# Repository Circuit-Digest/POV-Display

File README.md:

# [POV Display](https://circuitdigest.com/microcontroller-projects/diy-pov-display-using-ESP32-Arduino)

<br>

<br>

<be>

[DIY POV Display Tutorial using ESP32 Arduino](https://circuitdigest.com/microcontroller-projects/diy-pov-display-using-ESP32-Arduino)

[POV Display full Yoututbe Video](https://www.youtube.com/embed/gkemkTWuw_Q)

[<h1>Click here](https://circuitdigest.com/tags/ESP32) For other ESP32 tutorials.</h1>

<br>
<br>
<br>
<br>
<br>
<br>
<br>
Persistence of Vision is a fundamental principle that allows our eyes to perceive continuous motion from separate images, a concept crucial to the illusion of motion in cinema. When I was a kid, I was always fascinated with it. So, in this project, we are going to use this fascinating optical phenomenon to create a cool-looking POV Display. You must have seen a lot of such projects on the web, but most of them are limited to very low resolution and just display some texts and geometries. We plan to create a POV display that is not limited to just texts or simple shapes. Ours will be able to display images and animations with a resolution of 128 pixels. We have settled with this resolution because it's the sweet spot where we can get decent image quality and it would be easier to build.
 We settled on the ESP32 module as the brain of this display, because it is cheap, easy to get and powerful enough to run the display. The display will have two rotating arms, each outfitted with 64 LEDs, to create a total resolution of 128 pixels. The display will rotate at a constant speed, with the LEDs flashing in meticulously orchestrated patterns, controlled by the ESP32 microcontroller. This synchronization allows the display to generate images or text that appear to hover in mid-air, producing a smooth, continuous visual experience. 

<br>
[Note: As this projects are very simple we are only providing the code, schemaitic, and a few essential images if you want to get the images or code explanations do check out the Circuit Digest website.
<br>
<br>

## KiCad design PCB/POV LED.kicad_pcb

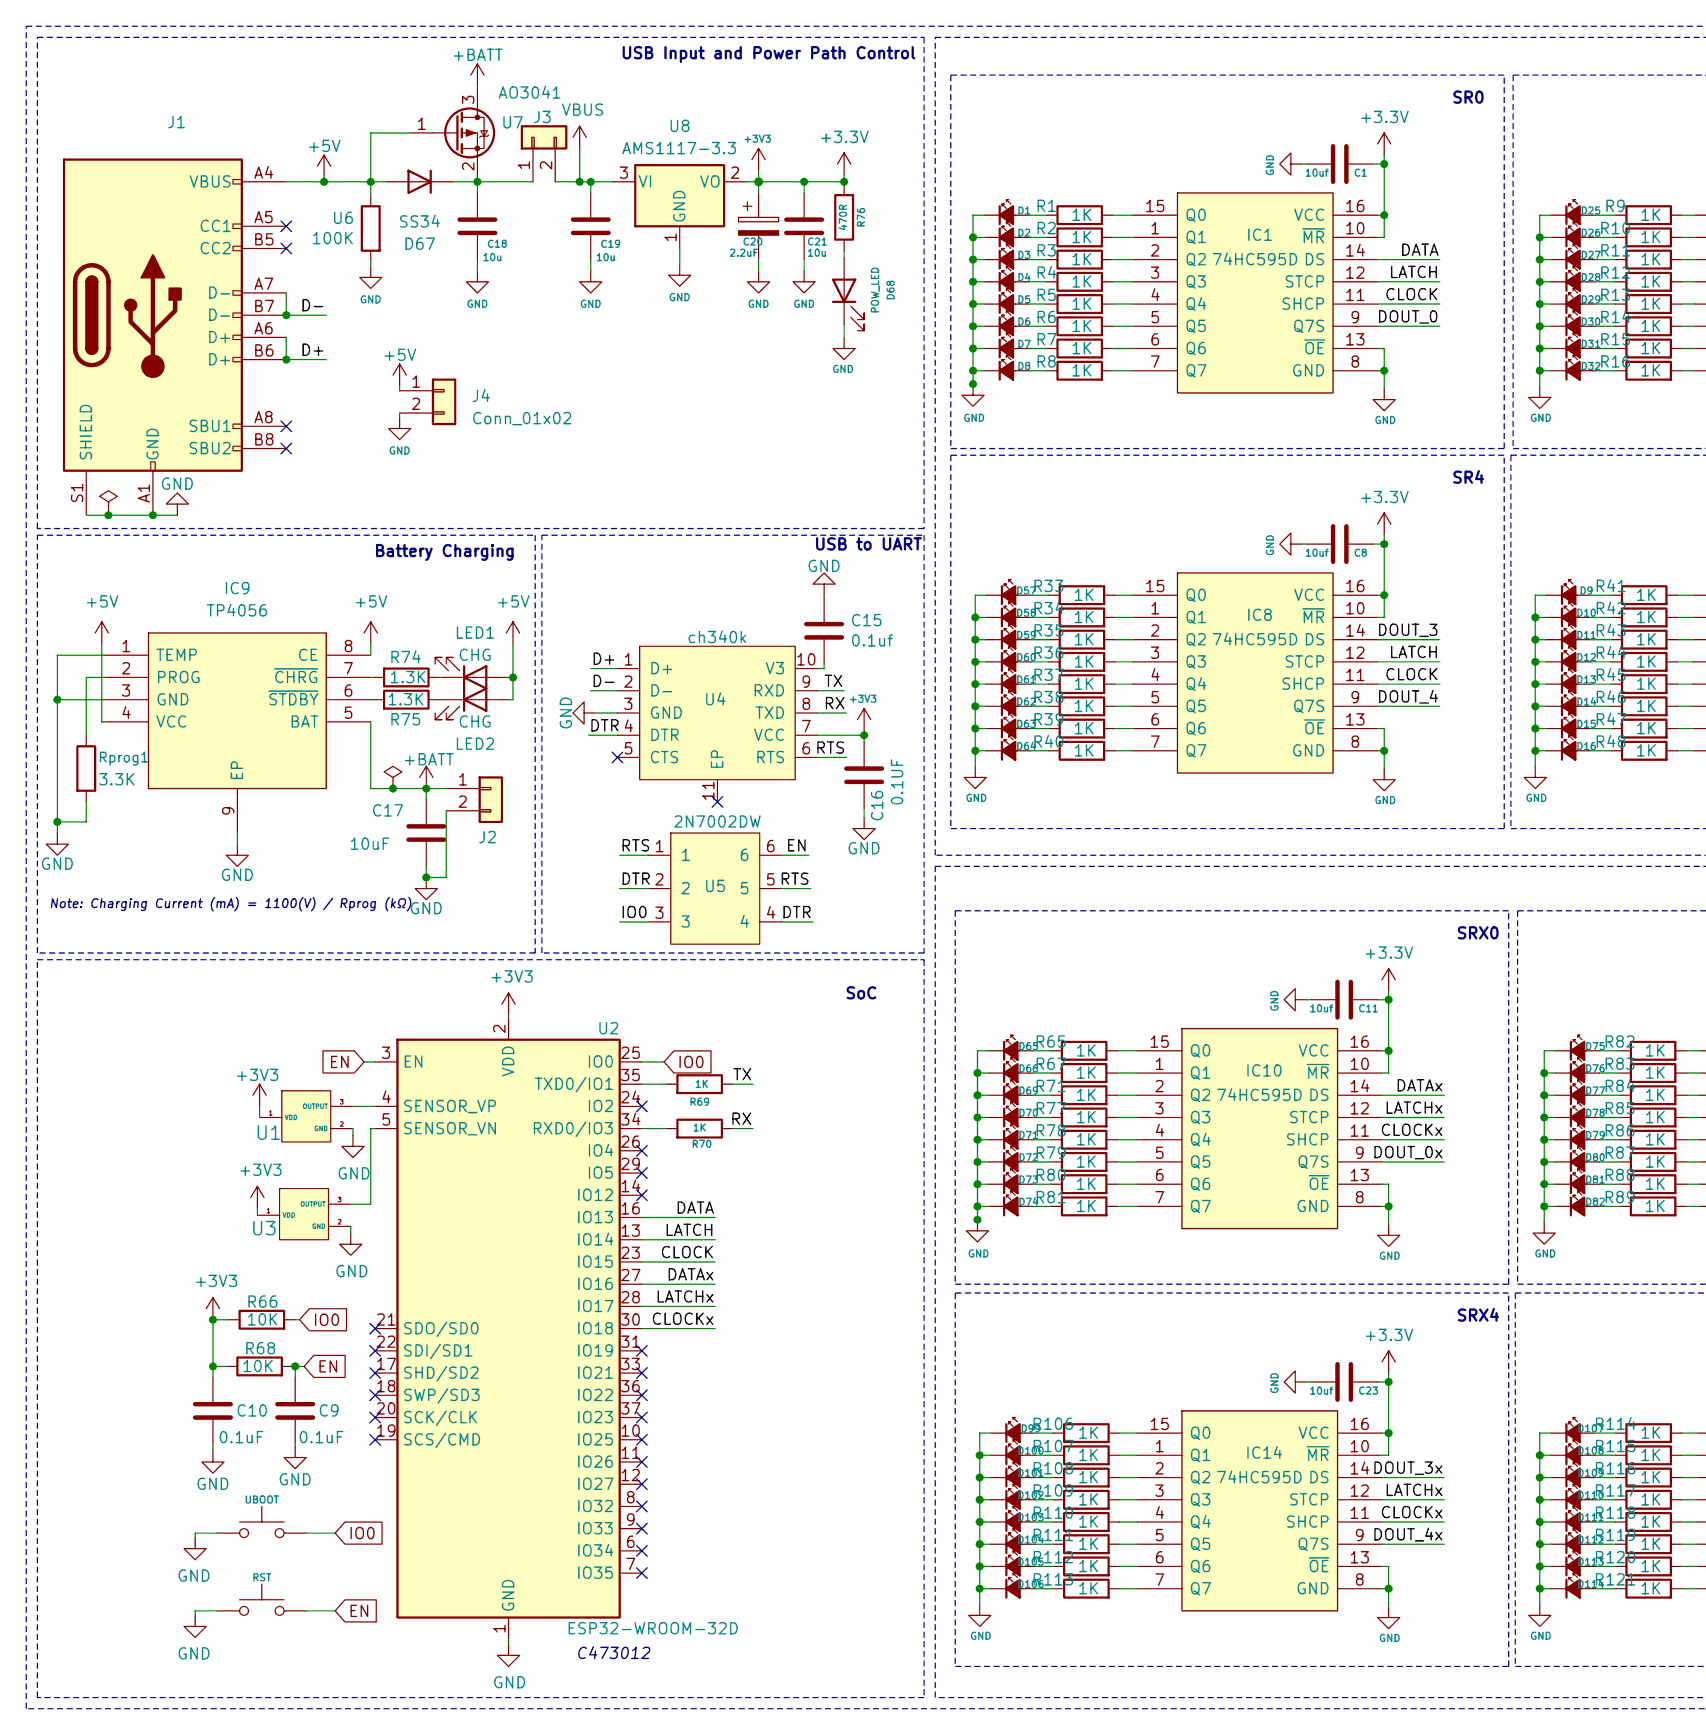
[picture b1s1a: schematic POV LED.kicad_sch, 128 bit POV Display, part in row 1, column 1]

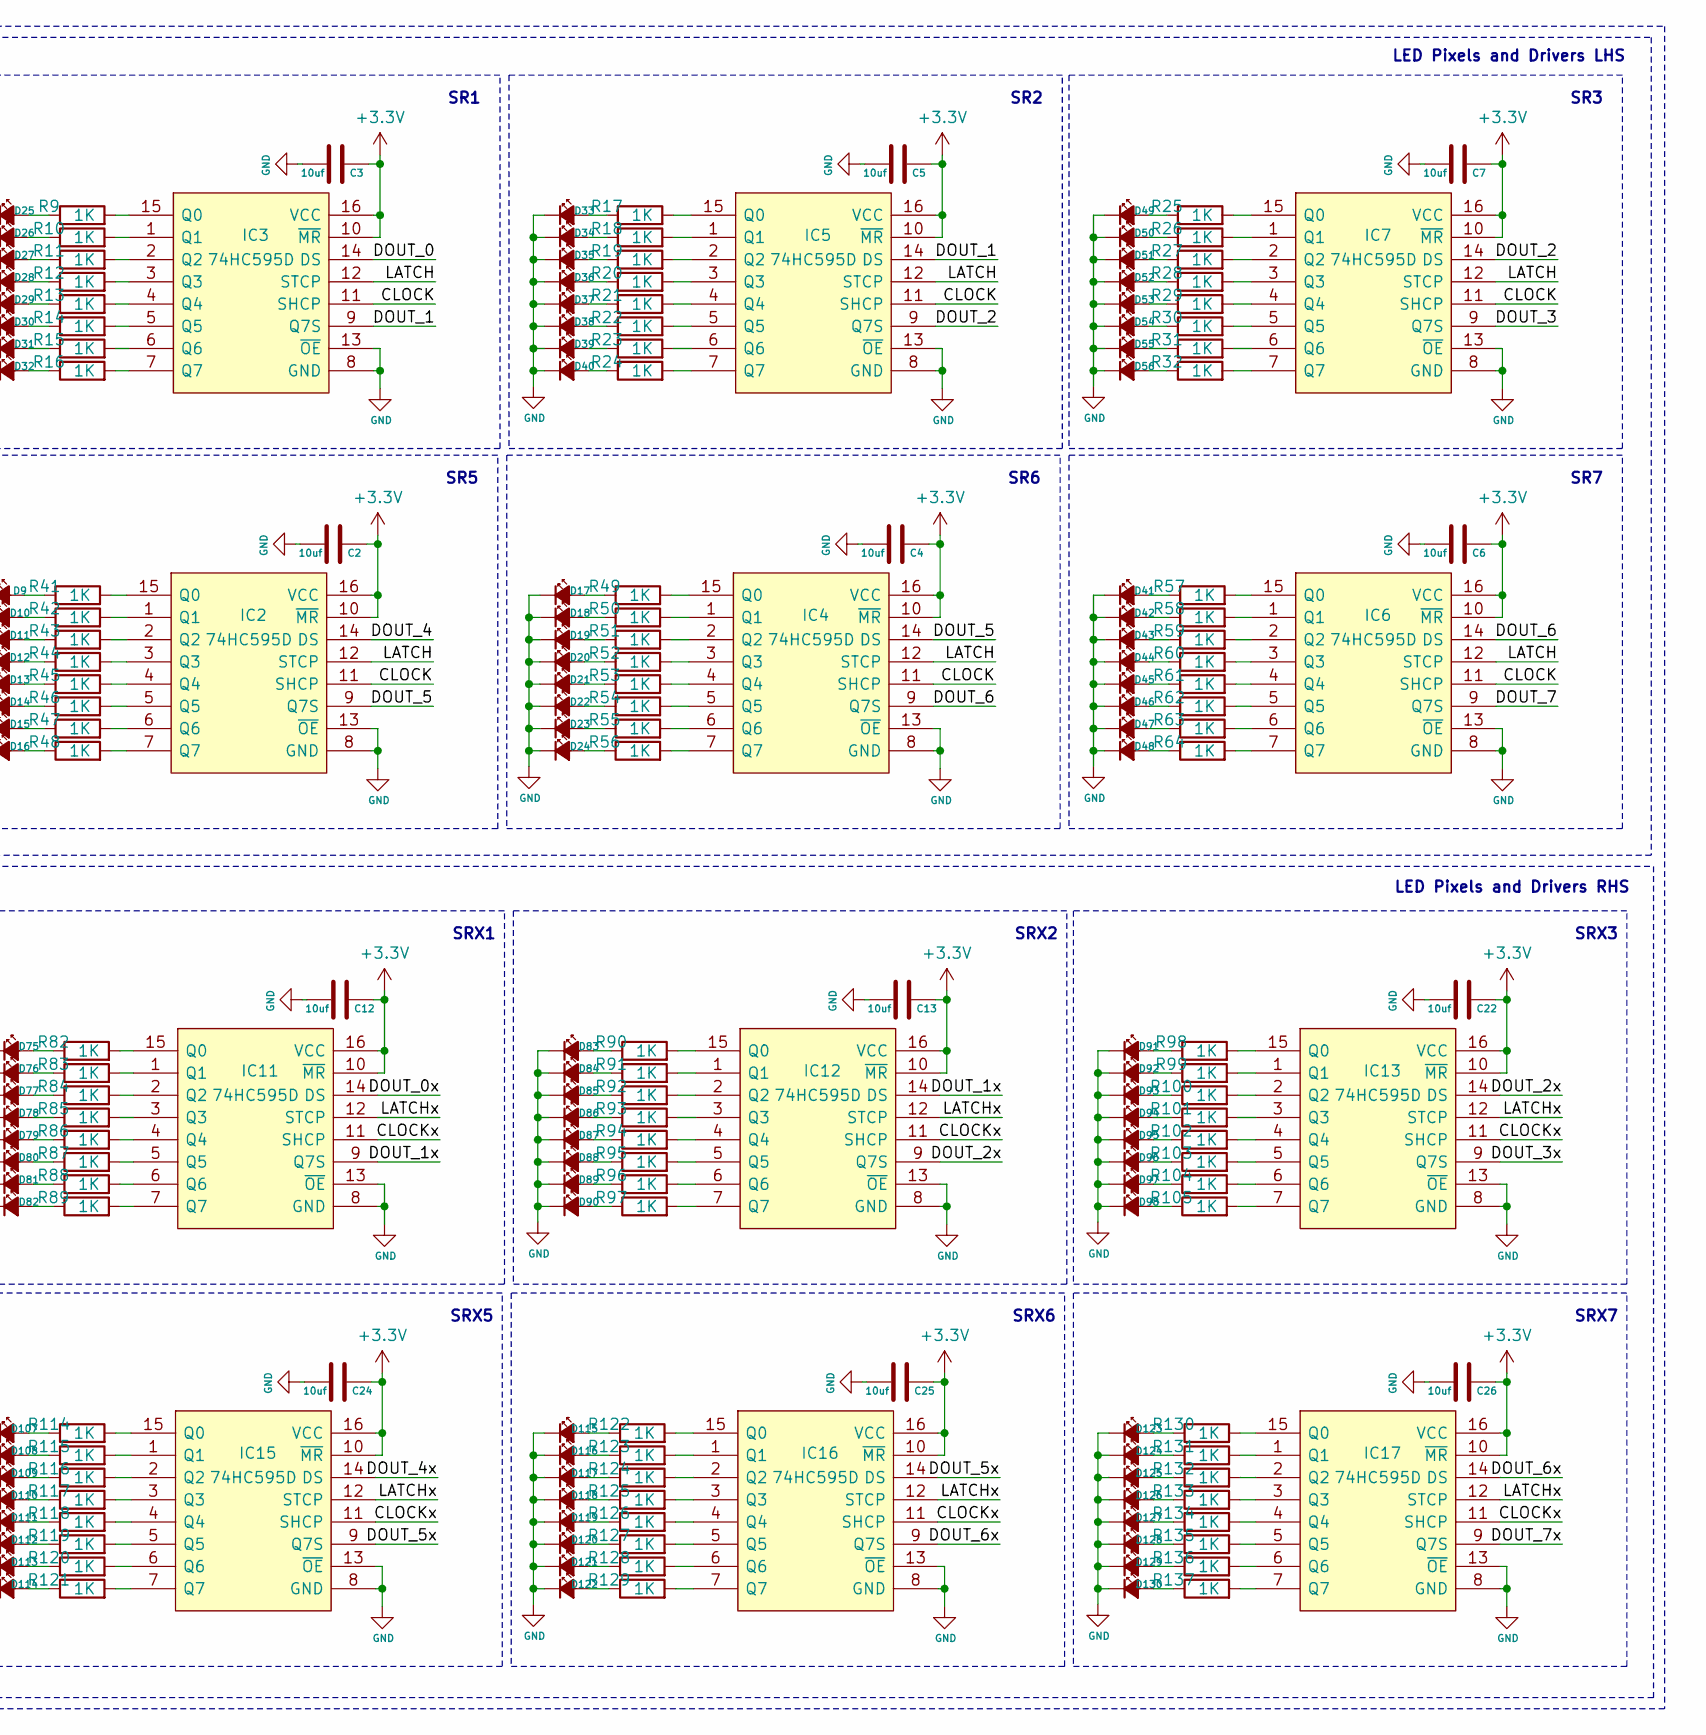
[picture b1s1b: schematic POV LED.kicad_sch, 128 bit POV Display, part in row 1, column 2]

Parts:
BOOT1: UBOOT; Tactile 3x4x2mm TS-A010
C1, C2, C3, C4, C5, C6, C7, C8, C11, C12, C13, C22, C23, C24, C25, C26: 10uf; C_0603_1608Metric
C9, C10: 0.1uF; C_0603_1608Metric
C15: 0.1uf; C_0603_1608Metric
C16: 0.1UF; C_0603_1608Metric
C17: 10uF; C_0603_1608Metric
C18, C19, C21: 10u; C_0603_1608Metric
C20: 2.2uF; C_0805_2012Metric
D1, D2, D3, D4, D5, D6, D7, D8, D9, D10, D11, D12, D13, D14, D15, D16, D17, D18, D19, D20, D21, D22, D23, D24, D25, D26, D27, D28, D29, D30, D31, D32, D33, D34, D35, D36, D37, D38, D39, D40, D41, D42, D43, D44, D45, D46, D47, D48, D49, D50, D51, D52, D53, D54, D55, D56, D57, D58, D59, D60, D61, D62, D63, D64, D65, D66, D69, D70, D71, D72, D73, D74, D75, D76, D77, D78, D79, D80, D81, D82, D83, D84, D85, D86, D87, D88, D89, D90, D91, D92, D93, D94, D95, D96, D97, D98, D99, D100, D101, D102, D103, D104, D105, D106, D107, D108, D109, D110, D111, D112, D113, D114, D115, D116, D117, D118, D119, D120, D121, D122, D123, D124, D125, D126, D127, D128, D129, D130: LED_Small_Filled; LED_0603_1608Metric
D67: SS34; D_SMA
D68: POW_LED; LED_0603_1608Metric
IC1, IC2, IC3, IC4, IC5, IC6, IC7, IC8, IC10, IC11, IC12, IC13, IC14, IC15, IC16, IC17: 74HC595D; 74HC595DQ100118; Mouser Part Number 771-74HC595D-Q100
IC9: TP4056; SOIC127P600X175-9N; Manufacturer_Part_Number TP4056-42-ESOP8
J1: USB_C_Receptacle_USB2.0; USB_C_Receptacle_HRO_TYPE-C-31-M-12
J2, J3: B2B-PH-SM4-TB(LF)(SN); JST_PH_B2B-PH-K_1x02_P2.00mm_Vertical
J4: Conn_01x02; PinHeader_1x02_P2.54mm_Vertical
LED1, LED2: CHG; LED_0603_1608Metric
R1, R2, R3, R4, R5, R6, R7, R8, R9, R10, R11, R12, R13, R14, R15, R16, R17, R18, R19, R20, R21, R22, R23, R24, R25, R26, R27, R28, R29, R30, R31, R32, R33, R34, R35, R36, R37, R38, R39, R40, R41, R42, R43, R44, R45, R46, R47, R48, R49, R50, R51, R52, R53, R54, R55, R56, R57, R58, R59, R60, R61, R62, R63, R64, R65, R67, R69, R70, R71, R77, R78, R79, R80, R81, R82, R83, R84, R85, R86, R87, R88, R89, R90, R91, R92, R93, R94, R95, R96, R97, R98, R99, R100, R101, R102, R103, R104, R105, R106, R107, R108, R109, R110, R111, R112, R113, R114, R115, R116, R117, R118, R119, R120, R121, R122, R123, R124, R125, R126, R127, R128, R129, R130, R131, R132, R133, R134, R135, R136, R137: 1K; R_0603_1608Metric
R66, R68: 10K; R_0603_1608Metric
R74, R75: 1.3K; R_0603_1608Metric
R76: 470R; R_0603_1608Metric
RST1: RST; Tactile 3x4x2mm TS-A010
Rprog1: 3.3K; R_0603_1608Metric
U1, U3: AH3572-SA-7; SOT23_AH3572-SA-7_DIO
U2: ESP32-WROOM-32D; ESP32-WROOM-32
U4: ch340k; ESSOP-10_3.9x4.9mm_P1.00mm
U5: 2N7002DW; SOT-363_SC-70-6
U6: 100K; R_0603_1608Metric
U7: AO3041; SOT-23
U8: AMS1117-3.3; SOT-223-3_TabPin2

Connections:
+3.3V: C1.1, C2.1, C3.1, C4.1, C5.1, C6.1, C7.1, C8.1, C10.1, C11.1, C12.1, C13.1, C16.2, C20.1, C21.1, C22.1, C23.1, C24.1, C25.1, C26.1, IC1.10 (~MR), IC1.16 (VCC), IC2.10 (~MR), IC2.16 (VCC), IC3.10 (~MR), IC3.16 (VCC), IC4.10 (~MR), IC4.16 (VCC), IC5.10 (~MR), IC5.16 (VCC), IC6.10 (~MR), IC6.16 (VCC), IC7.10 (~MR), IC7.16 (VCC), IC8.10 (~MR), IC8.16 (VCC), IC10.10 (~MR), IC10.16 (VCC), IC11.10 (~MR), IC11.16 (VCC), IC12.10 (~MR), IC12.16 (VCC), IC13.10 (~MR), IC13.16 (VCC), IC14.10 (~MR), IC14.16 (VCC), IC15.10 (~MR), IC15.16 (VCC), IC16.10 (~MR), IC16.16 (VCC), IC17.10 (~MR), IC17.16 (VCC), R66.1, R68.1, R76.2, U1.1 (VDD), U2.2 (VDD), U3.1 (VDD), U4.7 (VCC), U8.2 (VO)
+5V: D67.2 (A), IC9.4 (VCC), IC9.8 (CE), J1.A4 (VBUS), J1.A9 (VBUS), J1.B4 (VBUS), J1.B9 (VBUS), J4.1, LED1.2 (A), LED2.2 (A), U6.1, U7.1 (G)
+BATT: C17.1, IC9.5 (BAT), J2.1, U7.3 (D)
/CLOCK: IC1.11 (SHCP), IC2.11 (SHCP), IC3.11 (SHCP), IC4.11 (SHCP), IC5.11 (SHCP), IC6.11 (SHCP), IC7.11 (SHCP), IC8.11 (SHCP), U2.23 (IO15)
/CLOCKx: IC10.11 (SHCP), IC11.11 (SHCP), IC12.11 (SHCP), IC13.11 (SHCP), IC14.11 (SHCP), IC15.11 (SHCP), IC16.11 (SHCP), IC17.11 (SHCP), U2.30 (IO18)
/D+: J1.A6 (D+), J1.B6 (D+), U4.1 (D+)
/D-: J1.A7 (D-), J1.B7 (D-), U4.2 (D-)
/DATA: IC1.14 (DS), U2.16 (IO13)
/DATAx: IC10.14 (DS), U2.27 (IO16)
/DOUT_0: IC1.9 (Q7S), IC3.14 (DS)
/DOUT_0x: IC10.9 (Q7S), IC11.14 (DS)
/DOUT_1: IC3.9 (Q7S), IC5.14 (DS)
/DOUT_1x: IC11.9 (Q7S), IC12.14 (DS)
/DOUT_2: IC5.9 (Q7S), IC7.14 (DS)
/DOUT_2x: IC12.9 (Q7S), IC13.14 (DS)
/DOUT_3: IC7.9 (Q7S), IC8.14 (DS)
/DOUT_3x: IC13.9 (Q7S), IC14.14 (DS)
/DOUT_4: IC2.14 (DS), IC8.9 (Q7S)
/DOUT_4x: IC14.9 (Q7S), IC15.14 (DS)
/DOUT_5: IC2.9 (Q7S), IC4.14 (DS)
/DOUT_5x: IC15.9 (Q7S), IC16.14 (DS)
/DOUT_6: IC4.9 (Q7S), IC6.14 (DS)
/DOUT_6x: IC16.9 (Q7S), IC17.14 (DS)
/DOUT_7: IC6.9 (Q7S)
/DOUT_7x: IC17.9 (Q7S)
/DTR: U4.4 (DTR), U5.2, U5.4
/LATCH: IC1.12 (STCP), IC2.12 (STCP), IC3.12 (STCP), IC4.12 (STCP), IC5.12 (STCP), IC6.12 (STCP), IC7.12 (STCP), IC8.12 (STCP), U2.13 (IO14)
/LATCHx: IC10.12 (STCP), IC11.12 (STCP), IC12.12 (STCP), IC13.12 (STCP), IC14.12 (STCP), IC15.12 (STCP), IC16.12 (STCP), IC17.12 (STCP), U2.28 (IO17)
/RTS: U4.6 (RTS), U5.1, U5.5
/RX: R70.1, U4.8 (TXD)
/TX: R69.1, U4.9 (RXD)
EN: C9.1, R68.2, RST1.1, U2.3 (EN), U5.6
GND: BOOT1.2, C1.2, C2.2, C3.2, C4.2, C5.2, C6.2, C7.2, C8.2, C9.2, C10.2, C11.2, C12.2, C13.2, C15.1, C16.1, C17.2, C18.2, C19.2, C20.2, C21.2, C22.2, C23.2, C24.2, C25.2, C26.2, D1.1 (K), D2.1 (K), D3.1 (K), D4.1 (K), D5.1 (K), D6.1 (K), D7.1 (K), D8.1 (K), D9.1 (K), D10.1 (K), D11.1 (K), D12.1 (K), D13.1 (K), D14.1 (K), D15.1 (K), D16.1 (K), D17.1 (K), D18.1 (K), D19.1 (K), D20.1 (K), D21.1 (K), D22.1 (K), D23.1 (K), D24.1 (K), D25.1 (K), D26.1 (K), D27.1 (K), D28.1 (K), D29.1 (K), D30.1 (K), D31.1 (K), D32.1 (K), D33.1 (K), D34.1 (K), D35.1 (K), D36.1 (K), D37.1 (K), D38.1 (K), D39.1 (K), D40.1 (K), D41.1 (K), D42.1 (K), D43.1 (K), D44.1 (K), D45.1 (K), D46.1 (K), D47.1 (K), D48.1 (K), D49.1 (K), D50.1 (K), D51.1 (K), D52.1 (K), D53.1 (K), D54.1 (K), D55.1 (K), D56.1 (K), D57.1 (K), D58.1 (K), D59.1 (K), D60.1 (K), D61.1 (K), D62.1 (K), D63.1 (K), D64.1 (K), D65.1 (K), D66.1 (K), D68.1 (K), D69.1 (K), D70.1 (K), D71.1 (K), D72.1 (K), D73.1 (K), D74.1 (K), D75.1 (K), D76.1 (K), D77.1 (K), D78.1 (K), D79.1 (K), D80.1 (K), D81.1 (K), D82.1 (K), D83.1 (K), D84.1 (K), D85.1 (K), D86.1 (K), D87.1 (K), D88.1 (K), D89.1 (K), D90.1 (K), D91.1 (K), D92.1 (K), D93.1 (K), D94.1 (K), D95.1 (K), D96.1 (K), D97.1 (K), D98.1 (K), D99.1 (K), D100.1 (K), D101.1 (K), D102.1 (K), D103.1 (K), D104.1 (K), D105.1 (K), D106.1 (K), D107.1 (K), D108.1 (K), D109.1 (K), D110.1 (K), D111.1 (K), D112.1 (K), D113.1 (K), D114.1 (K), D115.1 (K), D116.1 (K), D117.1 (K), D118.1 (K), D119.1 (K), D120.1 (K), D121.1 (K), D122.1 (K), D123.1 (K), D124.1 (K), D125.1 (K), D126.1 (K), D127.1 (K), D128.1 (K), D129.1 (K), D130.1 (K), IC1.8 (GND), IC1.13 (~OE), IC2.8 (GND), IC2.13 (~OE), IC3.8 (GND), IC3.13 (~OE), IC4.8 (GND), IC4.13 (~OE), IC5.8 (GND), IC5.13 (~OE), IC6.8 (GND), IC6.13 (~OE), IC7.8 (GND), IC7.13 (~OE), IC8.8 (GND), IC8.13 (~OE), IC9.1 (TEMP), IC9.3 (GND), IC9.9 (EP), IC10.8 (GND), IC10.13 (~OE), IC11.8 (GND), IC11.13 (~OE), IC12.8 (GND), IC12.13 (~OE), IC13.8 (GND), IC13.13 (~OE), IC14.8 (GND), IC14.13 (~OE), IC15.8 (GND), IC15.13 (~OE), IC16.8 (GND), IC16.13 (~OE), IC17.8 (GND), IC17.13 (~OE), J1.A1 (GND), J1.A12 (GND), J1.B1 (GND), J1.B12 (GND), J1.S1 (SHIELD), J2.2, J4.2, RST1.2, Rprog1.2, U1.2 (GND), U2.1 (GND), U2.15 (GND), U2.38 (GND), U2.39 (GND), U3.2 (GND), U4.3 (GND), U6.2, U8.1 (GND)
IO0: BOOT1.1, R66.2, U2.25 (IO0), U5.3
unnamed: D1.2 (A), R1.1
unnamed: D2.2 (A), R2.1
unnamed: D3.2 (A), R3.1
unnamed: D4.2 (A), R4.1
unnamed: D5.2 (A), R5.1
unnamed: D6.2 (A), R6.1
unnamed: D7.2 (A), R7.1
unnamed: D8.2 (A), R8.1
unnamed: D9.2 (A), R41.1
unnamed: D10.2 (A), R42.1
unnamed: D11.2 (A), R43.1
unnamed: D12.2 (A), R44.1
unnamed: D13.2 (A), R45.1
unnamed: D14.2 (A), R46.1
unnamed: D15.2 (A), R47.1
unnamed: D16.2 (A), R48.1
unnamed: D17.2 (A), R49.1
unnamed: D18.2 (A), R50.1
unnamed: D19.2 (A), R51.1
unnamed: D20.2 (A), R52.1
unnamed: D21.2 (A), R53.1
unnamed: D22.2 (A), R54.1
unnamed: D23.2 (A), R55.1
unnamed: D24.2 (A), R56.1
unnamed: D25.2 (A), R9.1
unnamed: D26.2 (A), R10.1
unnamed: D27.2 (A), R11.1
unnamed: D28.2 (A), R12.1
unnamed: D29.2 (A), R13.1
unnamed: D30.2 (A), R14.1
unnamed: D31.2 (A), R15.1
unnamed: D32.2 (A), R16.1
unnamed: D33.2 (A), R17.1
unnamed: D34.2 (A), R18.1
unnamed: D35.2 (A), R19.1
unnamed: D36.2 (A), R20.1
unnamed: D37.2 (A), R21.1
unnamed: D38.2 (A), R22.1
unnamed: D39.2 (A), R23.1
unnamed: D40.2 (A), R24.1
unnamed: D41.2 (A), R57.1
unnamed: D42.2 (A), R58.1
unnamed: D43.2 (A), R59.1
unnamed: D44.2 (A), R60.1
unnamed: D45.2 (A), R61.1
unnamed: D46.2 (A), R62.1
unnamed: D47.2 (A), R63.1
unnamed: D48.2 (A), R64.1
unnamed: D49.2 (A), R25.1
unnamed: D50.2 (A), R26.1
unnamed: D51.2 (A), R27.1
unnamed: D52.2 (A), R28.1
unnamed: D53.2 (A), R29.1
unnamed: D54.2 (A), R30.1
unnamed: D55.2 (A), R31.1
unnamed: D56.2 (A), R32.1
unnamed: D57.2 (A), R33.1
unnamed: D58.2 (A), R34.1
unnamed: D59.2 (A), R35.1
unnamed: D60.2 (A), R36.1
unnamed: D61.2 (A), R37.1
unnamed: D62.2 (A), R38.1
unnamed: D63.2 (A), R39.1
unnamed: D64.2 (A), R40.1
unnamed: D65.2 (A), R65.1
unnamed: D66.2 (A), R67.1
unnamed: C18.1, D67.1 (K), J3.1, U7.2 (S)
unnamed: D68.2 (A), R76.1
unnamed: D69.2 (A), R71.1
unnamed: D70.2 (A), R77.1
unnamed: D71.2 (A), R78.1
unnamed: D72.2 (A), R79.1
unnamed: D73.2 (A), R80.1
unnamed: D74.2 (A), R81.1
unnamed: D75.2 (A), R82.1
unnamed: D76.2 (A), R83.1
unnamed: D77.2 (A), R84.1
unnamed: D78.2 (A), R85.1
unnamed: D79.2 (A), R86.1
unnamed: D80.2 (A), R87.1
unnamed: D81.2 (A), R88.1
unnamed: D82.2 (A), R89.1
unnamed: D83.2 (A), R90.1
unnamed: D84.2 (A), R91.1
unnamed: D85.2 (A), R92.1
unnamed: D86.2 (A), R93.1
unnamed: D87.2 (A), R94.1
unnamed: D88.2 (A), R95.1
unnamed: D89.2 (A), R96.1
unnamed: D90.2 (A), R97.1
unnamed: D91.2 (A), R98.1
unnamed: D92.2 (A), R99.1
unnamed: D93.2 (A), R100.1
unnamed: D94.2 (A), R101.1
unnamed: D95.2 (A), R102.1
unnamed: D96.2 (A), R103.1
unnamed: D97.2 (A), R104.1
unnamed: D98.2 (A), R105.1
unnamed: D99.2 (A), R106.1
unnamed: D100.2 (A), R107.1
unnamed: D101.2 (A), R108.1
unnamed: D102.2 (A), R109.1
unnamed: D103.2 (A), R110.1
unnamed: D104.2 (A), R111.1
unnamed: D105.2 (A), R112.1
unnamed: D106.2 (A), R113.1
unnamed: D107.2 (A), R114.1
unnamed: D108.2 (A), R115.1
unnamed: D109.2 (A), R116.1
unnamed: D110.2 (A), R117.1
unnamed: D111.2 (A), R118.1
unnamed: D112.2 (A), R119.1
unnamed: D113.2 (A), R120.1
unnamed: D114.2 (A), R121.1
unnamed: D115.2 (A), R122.1
unnamed: D116.2 (A), R123.1
unnamed: D117.2 (A), R124.1
unnamed: D118.2 (A), R125.1
unnamed: D119.2 (A), R126.1
unnamed: D120.2 (A), R127.1
unnamed: D121.2 (A), R128.1
unnamed: D122.2 (A), R129.1
unnamed: D123.2 (A), R130.1
unnamed: D124.2 (A), R131.1
unnamed: D125.2 (A), R132.1
unnamed: D126.2 (A), R133.1
unnamed: D127.2 (A), R134.1
unnamed: D128.2 (A), R135.1
unnamed: D129.2 (A), R136.1
unnamed: D130.2 (A), R137.1
unnamed: IC1.15 (Q0), R1.2
unnamed: IC1.1 (Q1), R2.2
unnamed: IC1.2 (Q2), R3.2
unnamed: IC1.3 (Q3), R4.2
unnamed: IC1.4 (Q4), R5.2
unnamed: IC1.5 (Q5), R6.2
unnamed: IC1.6 (Q6), R7.2
unnamed: IC1.7 (Q7), R8.2
unnamed: IC2.15 (Q0), R41.2
unnamed: IC2.1 (Q1), R42.2
unnamed: IC2.2 (Q2), R43.2
unnamed: IC2.3 (Q3), R44.2
unnamed: IC2.4 (Q4), R45.2
unnamed: IC2.5 (Q5), R46.2
unnamed: IC2.6 (Q6), R47.2
unnamed: IC2.7 (Q7), R48.2
unnamed: IC3.15 (Q0), R9.2
unnamed: IC3.1 (Q1), R10.2
unnamed: IC3.2 (Q2), R11.2
unnamed: IC3.3 (Q3), R12.2
unnamed: IC3.4 (Q4), R13.2
unnamed: IC3.5 (Q5), R14.2
unnamed: IC3.6 (Q6), R15.2
unnamed: IC3.7 (Q7), R16.2
unnamed: IC4.15 (Q0), R49.2
unnamed: IC4.1 (Q1), R50.2
unnamed: IC4.2 (Q2), R51.2
unnamed: IC4.3 (Q3), R52.2
unnamed: IC4.4 (Q4), R53.2
unnamed: IC4.5 (Q5), R54.2
unnamed: IC4.6 (Q6), R55.2
unnamed: IC4.7 (Q7), R56.2
unnamed: IC5.15 (Q0), R17.2
unnamed: IC5.1 (Q1), R18.2
unnamed: IC5.2 (Q2), R19.2
unnamed: IC5.3 (Q3), R20.2
unnamed: IC5.4 (Q4), R21.2
unnamed: IC5.5 (Q5), R22.2
unnamed: IC5.6 (Q6), R23.2
unnamed: IC5.7 (Q7), R24.2
unnamed: IC6.15 (Q0), R57.2
unnamed: IC6.1 (Q1), R58.2
unnamed: IC6.2 (Q2), R59.2
unnamed: IC6.3 (Q3), R60.2
unnamed: IC6.4 (Q4), R61.2
unnamed: IC6.5 (Q5), R62.2
unnamed: IC6.6 (Q6), R63.2
unnamed: IC6.7 (Q7), R64.2
unnamed: IC7.15 (Q0), R25.2
unnamed: IC7.1 (Q1), R26.2
unnamed: IC7.2 (Q2), R27.2
unnamed: IC7.3 (Q3), R28.2
unnamed: IC7.4 (Q4), R29.2
unnamed: IC7.5 (Q5), R30.2
unnamed: IC7.6 (Q6), R31.2
unnamed: IC7.7 (Q7), R32.2
unnamed: IC8.15 (Q0), R33.2
unnamed: IC8.1 (Q1), R34.2
unnamed: IC8.2 (Q2), R35.2
unnamed: IC8.3 (Q3), R36.2
unnamed: IC8.4 (Q4), R37.2
unnamed: IC8.5 (Q5), R38.2
unnamed: IC8.6 (Q6), R39.2
unnamed: IC8.7 (Q7), R40.2
unnamed: IC9.2 (PROG), Rprog1.1
unnamed: IC9.7 (~CHRG), R74.2
unnamed: IC9.6 (~STDBY), R75.2
unnamed: IC10.15 (Q0), R65.2
unnamed: IC10.1 (Q1), R67.2
unnamed: IC10.2 (Q2), R71.2
unnamed: IC10.3 (Q3), R77.2
unnamed: IC10.4 (Q4), R78.2
unnamed: IC10.5 (Q5), R79.2
unnamed: IC10.6 (Q6), R80.2
unnamed: IC10.7 (Q7), R81.2
unnamed: IC11.15 (Q0), R82.2
unnamed: IC11.1 (Q1), R83.2
unnamed: IC11.2 (Q2), R84.2
unnamed: IC11.3 (Q3), R85.2
unnamed: IC11.4 (Q4), R86.2
unnamed: IC11.5 (Q5), R87.2
unnamed: IC11.6 (Q6), R88.2
unnamed: IC11.7 (Q7), R89.2
unnamed: IC12.15 (Q0), R90.2
unnamed: IC12.1 (Q1), R91.2
unnamed: IC12.2 (Q2), R92.2
unnamed: IC12.3 (Q3), R93.2
unnamed: IC12.4 (Q4), R94.2
unnamed: IC12.5 (Q5), R95.2
unnamed: IC12.6 (Q6), R96.2
unnamed: IC12.7 (Q7), R97.2
unnamed: IC13.15 (Q0), R98.2
unnamed: IC13.1 (Q1), R99.2
unnamed: IC13.2 (Q2), R100.2
unnamed: IC13.3 (Q3), R101.2
unnamed: IC13.4 (Q4), R102.2
unnamed: IC13.5 (Q5), R103.2
unnamed: IC13.6 (Q6), R104.2
unnamed: IC13.7 (Q7), R105.2
unnamed: IC14.15 (Q0), R106.2
unnamed: IC14.1 (Q1), R107.2
unnamed: IC14.2 (Q2), R108.2
unnamed: IC14.3 (Q3), R109.2
unnamed: IC14.4 (Q4), R110.2
unnamed: IC14.5 (Q5), R111.2
unnamed: IC14.6 (Q6), R112.2
unnamed: IC14.7 (Q7), R113.2
unnamed: IC15.15 (Q0), R114.2
unnamed: IC15.1 (Q1), R115.2
unnamed: IC15.2 (Q2), R116.2
unnamed: IC15.3 (Q3), R117.2
unnamed: IC15.4 (Q4), R118.2
unnamed: IC15.5 (Q5), R119.2
unnamed: IC15.6 (Q6), R120.2
unnamed: IC15.7 (Q7), R121.2
unnamed: IC16.15 (Q0), R122.2
unnamed: IC16.1 (Q1), R123.2
unnamed: IC16.2 (Q2), R124.2
unnamed: IC16.3 (Q3), R125.2
unnamed: IC16.4 (Q4), R126.2
unnamed: IC16.5 (Q5), R127.2
unnamed: IC16.6 (Q6), R128.2
unnamed: IC16.7 (Q7), R129.2
unnamed: IC17.15 (Q0), R130.2
unnamed: IC17.1 (Q1), R131.2
unnamed: IC17.2 (Q2), R132.2
unnamed: IC17.3 (Q3), R133.2
unnamed: IC17.4 (Q4), R134.2
unnamed: IC17.5 (Q5), R135.2
unnamed: IC17.6 (Q6), R136.2
unnamed: IC17.7 (Q7), R137.2
unnamed: LED1.1 (K), R74.1
unnamed: LED2.1 (K), R75.1
unnamed: U1.3 (OUTPUT), U2.4 (SENSOR_VP)
unnamed: R70.2, U2.34 (RXD0/IO3)
unnamed: U2.5 (SENSOR_VN), U3.3 (OUTPUT)
unnamed: R69.2, U2.35 (TXD0/IO1)
unnamed: C15.2, U4.10 (V3)
VBUS: C19.1, J3.2, U8.3 (VI)

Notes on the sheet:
Note: Charging Current (mA) = 1100(V) / Rprog (kΩ)
SRX6
SRX1
SRX3
SoC
USB to UART
LED Pixels and Drivers LHS
Battery Charging
LED Pixels and Drivers RHS
SR4
SR7
SR1
SRX0
USB Input and Power Path Control
SR3
SR0
C473012
SR2
SRX5
SRX7
SR5
SRX4
SRX2
SR6

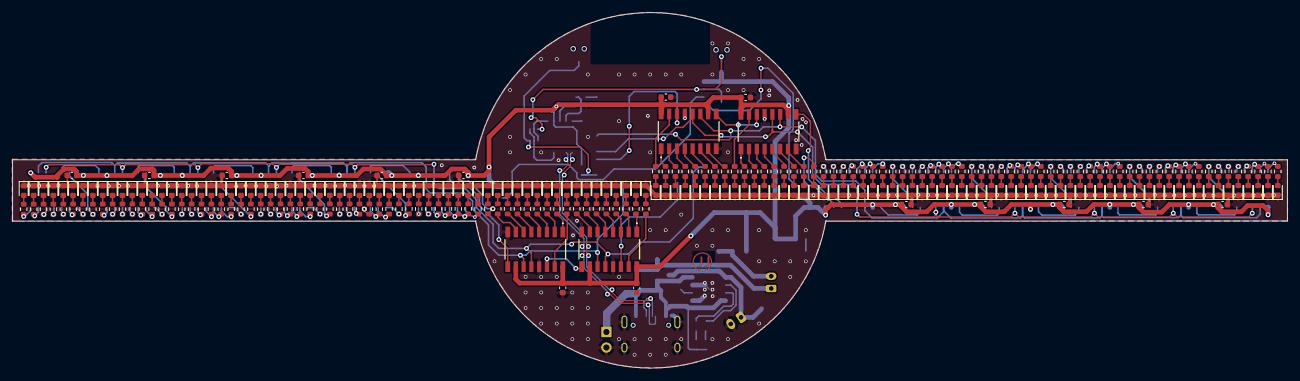
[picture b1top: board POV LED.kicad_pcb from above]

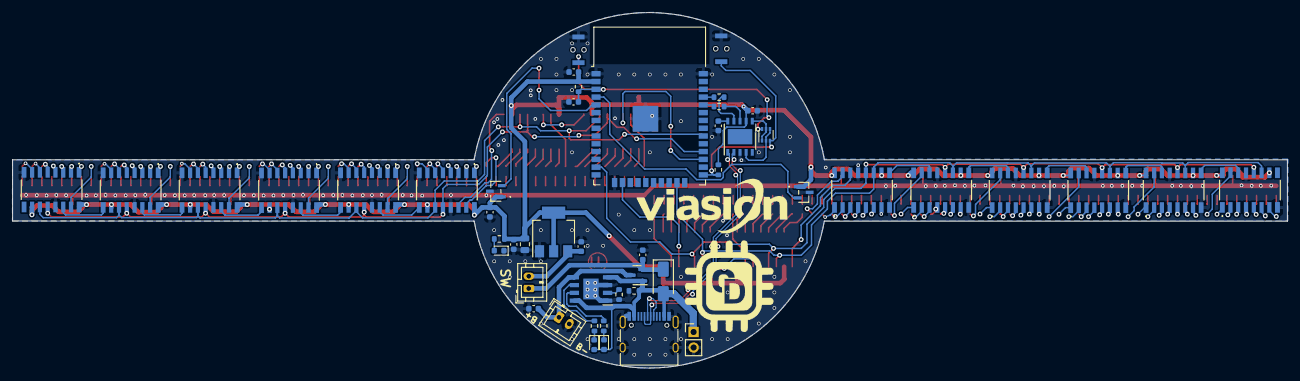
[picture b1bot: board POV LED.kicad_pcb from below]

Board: 2 copper layers, 208.0 x 58.0 mm, 324 parts (49 on the bottom side), 301 nets.

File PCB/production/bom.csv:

Designator,Footprint,Quantity,Value,LCSC Part #
BOOT1,Tactile 3x4x2mm TS-A010,1,UBOOT,
"C1, C11, C12, C13, C17, C2, C22, C23, C24, C25, C26, C3, C4, C5, C6, C7, C8",0603,17,10uf,
"C10, C15, C16, C9",0603,4,0.1uF,
"C18, C19, C21",0603,3,10u,
C20,0805,1,2.2uF,
"D1, D10, D100, D101, D102, D103, D104, D105, D106, D107, D108, D109, D11, D110, D111, D112, D113, D114, D115, D116, D117, D118, D119, D12, D120, D121, D122, D123, D124, D125, D126, D127, D128, D129, D13, D130, D14, D15, D16, D17, D18, D19, D2, D20, D21, D22, D23, D24, D25, D26, D27, D28, D29, D3, D30, D31, D32, D33, D34, D35, D36, D37, D38, D39, D4, D40, D41, D42, D43, D44, D45, D46, D47, D48, D49, D5, D50, D51, D52, D53, D54, D55, D56, D57, D58, D59, D6, D60, D61, D62, D63, D64, D65, D66, D69, D7, D70, D71, D72, D73, D74, D75, D76, D77, D78, D79, D8, D80, D81, D82, D83, D84, D85, D86, D87, D88, D89, D9, D90, D91, D92, D93, D94, D95, D96, D97, D98, D99",0603,128,LED_Small_Filled,
D67,D_SMA,1,SS34,
D68,0603,1,POW_LED,
"IC1, IC10, IC11, IC12, IC13, IC14, IC15, IC16, IC17, IC2, IC3, IC4, IC5, IC6, IC7, IC8",74HC595DQ100118,16,74HC595D,
IC9,SOIC127P600X175-9N,1,TP4056,
J1,USB_C_Receptacle_HRO_TYPE-C-31-M-12,1,USB_C_Receptacle_USB2.0,
"J2, J3",JST_PH_B2B-PH-K_1x02_P2.00mm_Vertical,2, B2B-PH-SM4-TB(LF)(SN) ,
J4,PinHeader_1x02_P2.54mm_Vertical,1,Conn_01x02,
"LED1, LED2",0603,2,CHG,
"R1, R10, R100, R101, R102, R103, R104, R105, R106, R107, R108, R109, R11, R110, R111, R112, R113, R114, R115, R116, R117, R118, R119, R12, R120, R121, R122, R123, R124, R125, R126, R127, R128, R129, R13, R130, R131, R132, R133, R134, R135, R136, R137, R14, R15, R16, R17, R18, R19, R2, R20, R21, R22, R23, R24, R25, R26, R27, R28, R29, R3, R30, R31, R32, R33, R34, R35, R36, R37, R38, R39, R4, R40, R41, R42, R43, R44, R45, R46, R47, R48, R49, R5, R50, R51, R52, R53, R54, R55, R56, R57, R58, R59, R6, R60, R61, R62, R63, R64, R65, R67, R69, R7, R70, R71, R77, R78, R79, R8, R80, R81, R82, R83, R84, R85, R86, R87, R88, R89, R9, R90, R91, R92, R93, R94, R95, R96, R97, R98, R99",0603,130,1K,
"R66, R68",0603,2,10K,
"R74, R75",0603,2,1.3K,
R76,0603,1,470R,
RST1,Tactile 3x4x2mm TS-A010,1,RST,
Rprog1,0603,1,3.3K,
"U1, U3",SOT23_AH3572-SA-7_DIO,2,AH3572-SA-7,
U2,ESP32-WROOM-32,1,ESP32-WROOM-32D,
U4,ESSOP-10_3.9x4.9mm_P1.00mm,1,ch340k,
U5,SOT-363_SC-70-6,1,DDC114TU-7-F,
U6,0603,1,100K,
U7,SOT-23,1,AO3041,
U8,SOT-223-3_TabPin2,1,AMS1117-3.3,

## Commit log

2024-03-01 Create j
2024-03-01 Create k
2024-03-01 Create l
